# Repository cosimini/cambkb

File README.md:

# Yet another split keyboard with low profile Gateron switches

**Important note: tested, it works**
Now the hard part, try getting used to it.

**WARNING:** There's a mistake in the RJ-9 connector routing, I didn't consider that RJ9 cables are typically crimped mirrored, so a custom cable has to be made in order to use the design.

Basically a replica of any other split keyboard project you can find on github
* Pro micro controller
* Gateron low profile KS-33 switches with hot-swap sockets
* No OLED screen, LEDs or other shiny stuff

The main difference in the layout is that the positions of the thumb-keys is moved to the center with respect to more famous keyboards like the Lily58, more like the Voyager.
Vertical stagging of about 1/4 of a key size is applied in the vertical direction, between columns.
The distance between switches is 19mm and not 19.05mm like many other, I don't care it's not 3/4 of an inch.

The PCB is designed using KiCad. It is the same for both right and left side, depending on where components are soldered.
There's no 3D printed case or key support mask, but I'd like to implement it.

The reason for the double socket for the controller is that I was usure on which side I'd like to put the controller.

For the time being I'm not planning to implement QMK or similar things, key map is hardcoded in the code.
The code is based on the Arduino library because I'm lazy. For the same reason I'm using PlatformIO.

For the used switches and controller lib/footprint, credit to [foostan/kdb](https://github.com/foostan/kbd/tree/main).

# BOM
* Controllers: Any pro-micro close is fine, I used the cheapest one I found on Amazon. You can buy presoldered ones, the PCB is compatible with any orientation.
* Switches: Gatheron low profile switches, KS-33 footprint, I used [those ones](https://www.gateron.com/products/gateron-ks-33-low-profile-20-banana-switch?VariantsId=10734).
* Sockets for the switches: The ones associated to the KS-33 footprint ([those](https://www.gateron.com/products/gateron-low-profile-switch-hot-swap-pcb-socket?VariantsId=10234)).
* Diodes: BAT85 are the ones I used, but any signal diode with similar specs should be fine.
* Resistors: There's a resistor in series to the voltage sourcing pin. To prevent accidental shorts, a 1k resistor is placed in series. Those can be replaced by a jumper wire. Note I used DIN0204, a kind of small size trough hole package.
* Sockets for the controller: If you don't want to solder the controllers to the PCB, you can use any 2.54mm socket.
* RJ9 socket: It is a standard, any trough hole socket is fine.
* RJ9 Cable: **WARNING** as mentioned above, you need to make your own cable, as the common telephone ones has mirrored connected plugs at each end (i.e. in my design each cable must end on the same size of the plug).

# Pictures of the result

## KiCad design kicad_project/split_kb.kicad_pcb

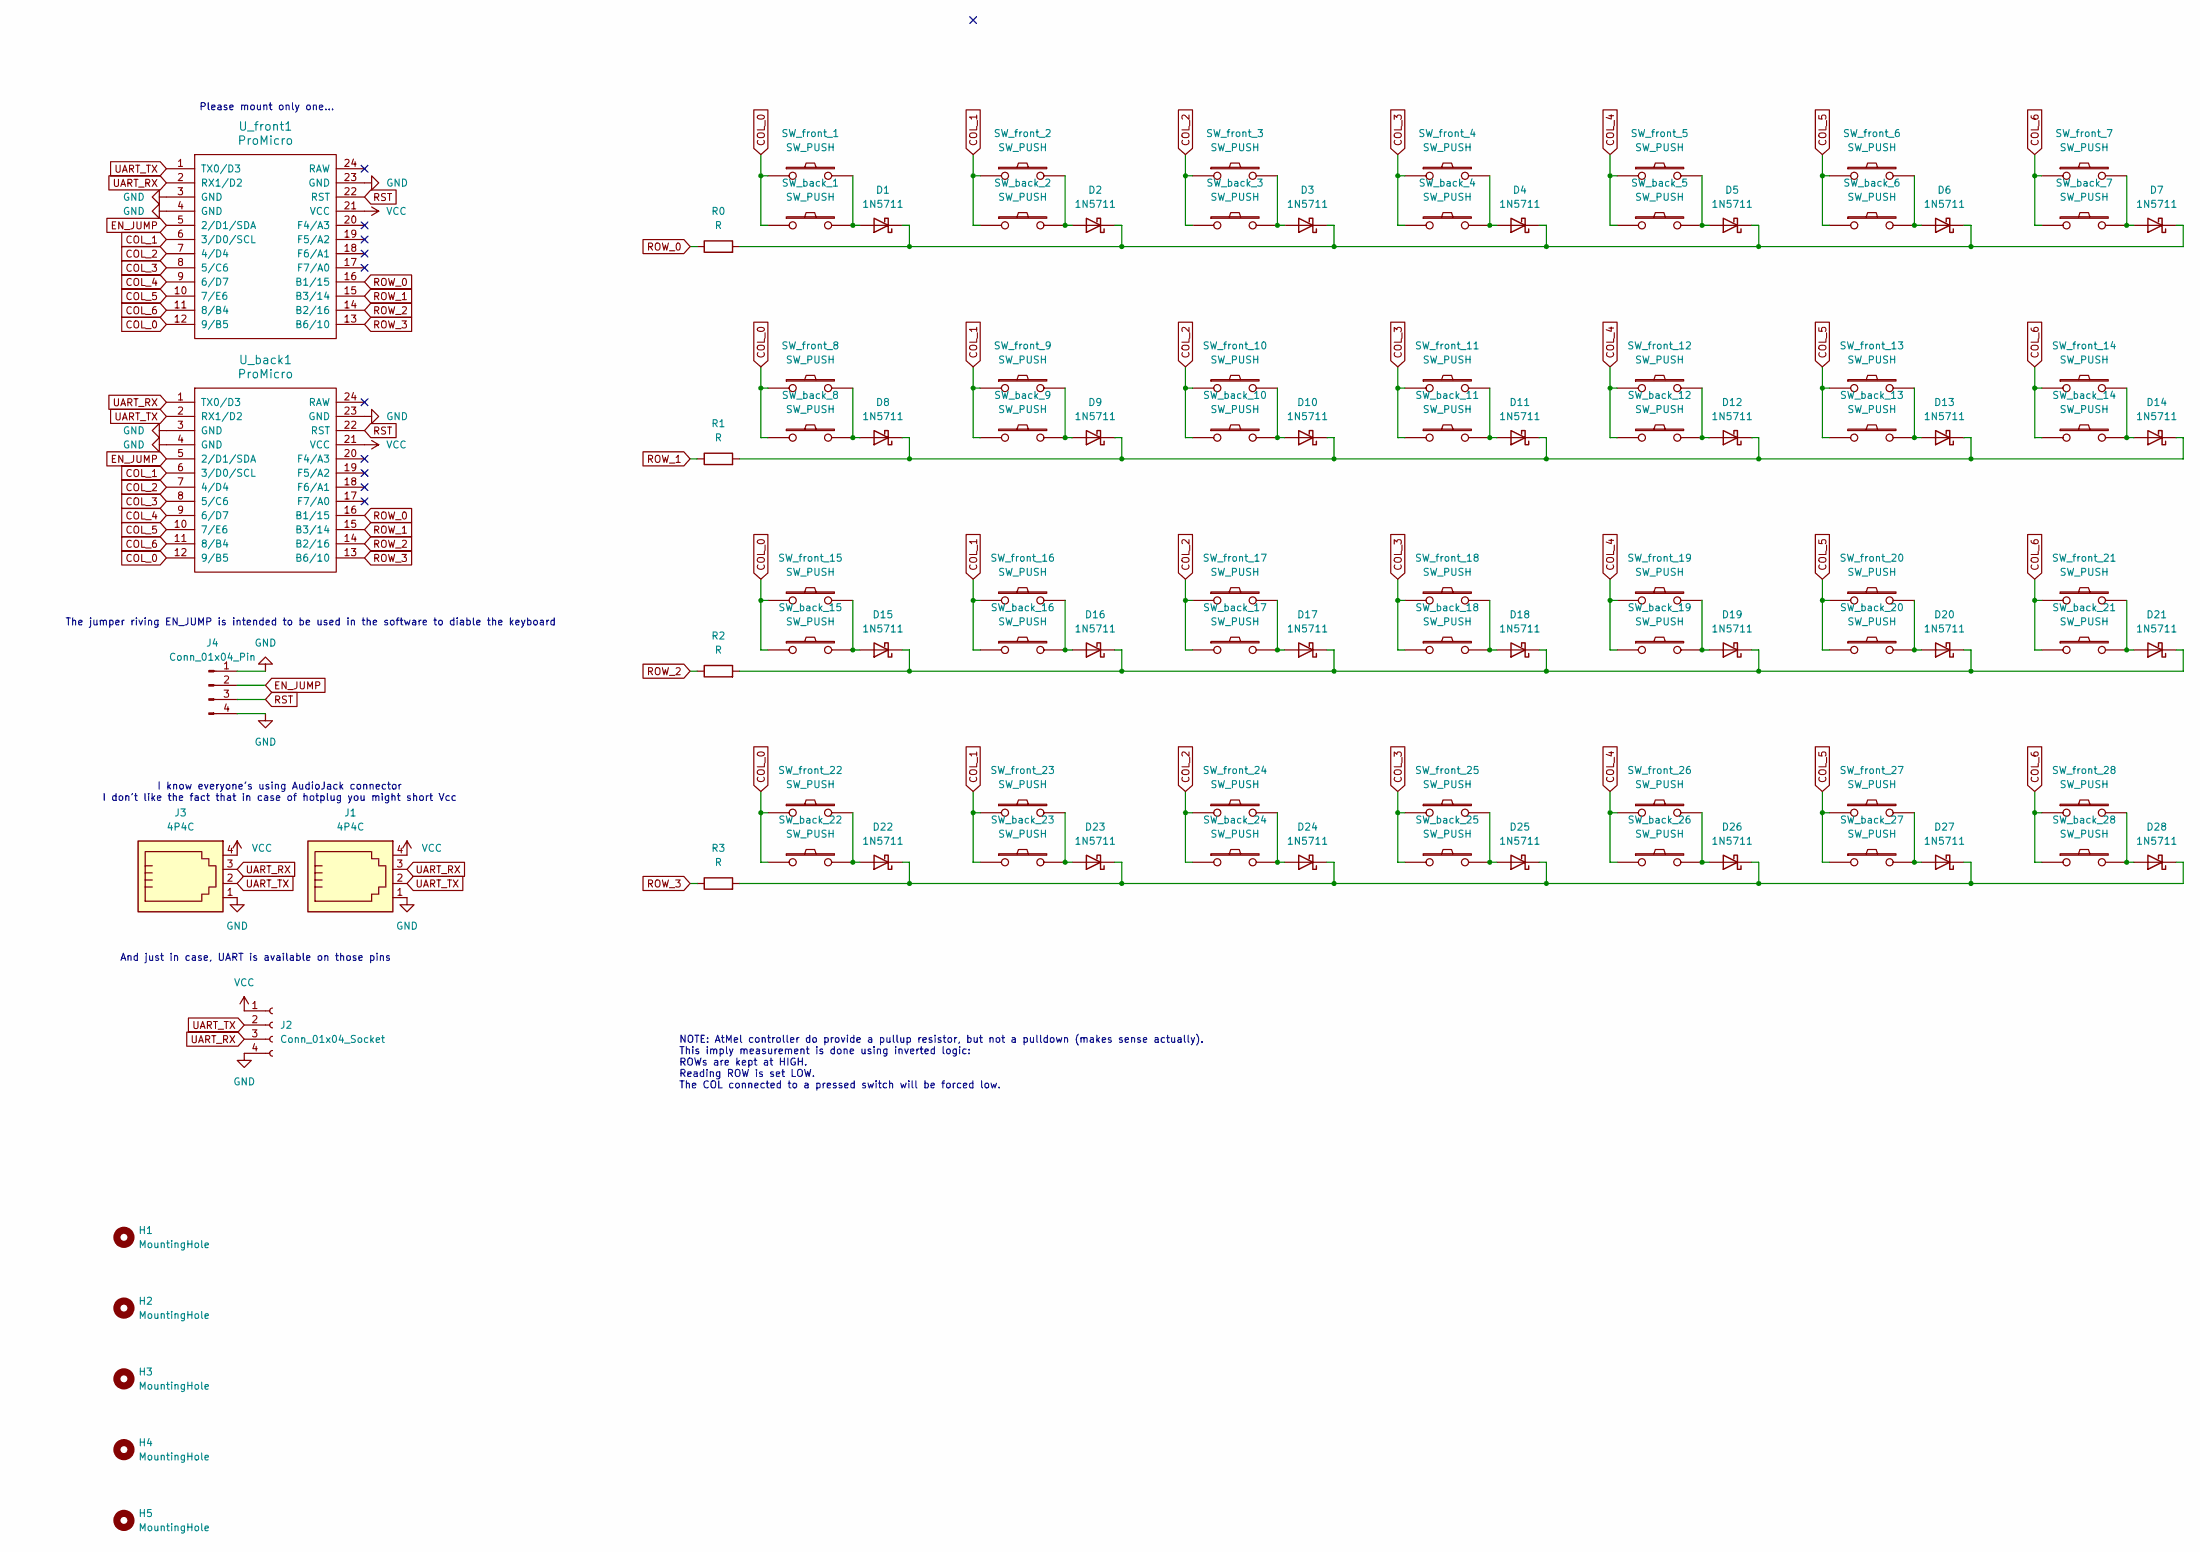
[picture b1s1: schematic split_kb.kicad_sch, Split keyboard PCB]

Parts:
D1, D2, D3, D4, D5, D6, D7, D8, D9, D10, D11, D12, D13, D14, D15, D16, D17, D18, D19, D20, D21, D22, D23, D24, D25, D26, D27, D28: 1N5711; D_DO-35_SOD27_P7.62mm_Horizontal
H1, H2, H3, H4, H5: MountingHole; MountingHole_3mm_Pad_Via
J1, J3: 4P4C; RJ9_Evercom_5301-440xxx_Horizontal
J2: Conn_01x04_Socket; PinHeader_1x04_P2.54mm_Vertical
J4: Conn_01x04_Pin; PinHeader_1x04_P2.54mm_Vertical
R0, R1, R2, R3: R; R_Axial_DIN0204_L3.6mm_D1.6mm_P5.08mm_Horizontal
SW_back_1, SW_back_2, SW_back_3, SW_back_4, SW_back_5, SW_back_6, SW_back_7, SW_back_8, SW_back_9, SW_back_10, SW_back_11, SW_back_12, SW_back_13, SW_back_14, SW_back_15, SW_back_16, SW_back_17, SW_back_18, SW_back_19, SW_back_20, SW_back_21, SW_back_22, SW_back_23, SW_back_24, SW_back_25, SW_back_26, SW_back_27, SW_back_28: SW_PUSH; keyswitch_gateron_low_profile_hotswap_1u
SW_front_1, SW_front_2, SW_front_3, SW_front_4, SW_front_5, SW_front_6, SW_front_7, SW_front_8, SW_front_9, SW_front_10, SW_front_11, SW_front_12, SW_front_13, SW_front_14, SW_front_15, SW_front_16, SW_front_17, SW_front_18, SW_front_19, SW_front_20, SW_front_21, SW_front_22, SW_front_23, SW_front_24, SW_front_25, SW_front_26, SW_front_27, SW_front_28: SW_PUSH; keyswitch_gateron_low_profile_hotswap_1u
U_back1: ProMicro
U_front1: ProMicro

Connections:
COL_0: SW_back_1.1, SW_back_8.1, SW_back_15.1, SW_back_22.1, SW_front_1.1, SW_front_8.1, SW_front_15.1, SW_front_22.1, U_back1.12 (9/B5), U_front1.12 (9/B5)
COL_1: SW_back_2.1, SW_back_9.1, SW_back_16.1, SW_back_23.1, SW_front_2.1, SW_front_9.1, SW_front_16.1, SW_front_23.1, U_back1.6 (3/D0/SCL), U_front1.6 (3/D0/SCL)
COL_2: SW_back_3.1, SW_back_10.1, SW_back_17.1, SW_back_24.1, SW_front_3.1, SW_front_10.1, SW_front_17.1, SW_front_24.1, U_back1.7 (4/D4), U_front1.7 (4/D4)
COL_3: SW_back_4.1, SW_back_11.1, SW_back_18.1, SW_back_25.1, SW_front_4.1, SW_front_11.1, SW_front_18.1, SW_front_25.1, U_back1.8 (5/C6), U_front1.8 (5/C6)
COL_4: SW_back_5.1, SW_back_12.1, SW_back_19.1, SW_back_26.1, SW_front_5.1, SW_front_12.1, SW_front_19.1, SW_front_26.1, U_back1.9 (6/D7), U_front1.9 (6/D7)
COL_5: SW_back_6.1, SW_back_13.1, SW_back_20.1, SW_back_27.1, SW_front_6.1, SW_front_13.1, SW_front_20.1, SW_front_27.1, U_back1.10 (7/E6), U_front1.10 (7/E6)
COL_6: SW_back_7.1, SW_back_14.1, SW_back_21.1, SW_back_28.1, SW_front_7.1, SW_front_14.1, SW_front_21.1, SW_front_28.1, U_back1.11 (8/B4), U_front1.11 (8/B4)
EN_JUMP: J4.2, U_back1.5 (2/D1/SDA), U_front1.5 (2/D1/SDA)
GND: J1.1, J2.4, J3.1, J4.1, J4.4, U_back1.3 (GND), U_back1.4 (GND), U_back1.23 (GND), U_front1.3 (GND), U_front1.4 (GND), U_front1.23 (GND)
unnamed: D1.2 (A), SW_back_1.2, SW_front_1.2
unnamed: D1.1 (K), D2.1 (K), D3.1 (K), D4.1 (K), D5.1 (K), D6.1 (K), D7.1 (K), R0.2
unnamed: D2.2 (A), SW_back_2.2, SW_front_2.2
unnamed: D3.2 (A), SW_back_3.2, SW_front_3.2
unnamed: D4.2 (A), SW_back_4.2, SW_front_4.2
unnamed: D5.2 (A), SW_back_5.2, SW_front_5.2
unnamed: D6.2 (A), SW_back_6.2, SW_front_6.2
unnamed: D7.2 (A), SW_back_7.2, SW_front_7.2
unnamed: D8.2 (A), SW_back_8.2, SW_front_8.2
unnamed: D9.2 (A), SW_back_9.2, SW_front_9.2
unnamed: D10.2 (A), SW_back_10.2, SW_front_10.2
unnamed: D8.1 (K), D9.1 (K), D10.1 (K), D11.1 (K), D12.1 (K), D13.1 (K), D14.1 (K), R1.2
unnamed: D11.2 (A), SW_back_11.2, SW_front_11.2
unnamed: D12.2 (A), SW_back_12.2, SW_front_12.2
unnamed: D13.2 (A), SW_back_13.2, SW_front_13.2
unnamed: D14.2 (A), SW_back_14.2, SW_front_14.2
unnamed: D15.2 (A), SW_back_15.2, SW_front_15.2
unnamed: D15.1 (K), D16.1 (K), D17.1 (K), D18.1 (K), D19.1 (K), D20.1 (K), D21.1 (K), R2.2
unnamed: D16.2 (A), SW_back_16.2, SW_front_16.2
unnamed: D17.2 (A), SW_back_17.2, SW_front_17.2
unnamed: D18.2 (A), SW_back_18.2, SW_front_18.2
unnamed: D19.2 (A), SW_back_19.2, SW_front_19.2
unnamed: D20.2 (A), SW_back_20.2, SW_front_20.2
unnamed: D21.2 (A), SW_back_21.2, SW_front_21.2
unnamed: D22.2 (A), SW_back_22.2, SW_front_22.2
unnamed: D22.1 (K), D23.1 (K), D24.1 (K), D25.1 (K), D26.1 (K), D27.1 (K), D28.1 (K), R3.2
unnamed: D23.2 (A), SW_back_23.2, SW_front_23.2
unnamed: D24.2 (A), SW_back_24.2, SW_front_24.2
unnamed: D25.2 (A), SW_back_25.2, SW_front_25.2
unnamed: D26.2 (A), SW_back_26.2, SW_front_26.2
unnamed: D27.2 (A), SW_back_27.2, SW_front_27.2
unnamed: D28.2 (A), SW_back_28.2, SW_front_28.2
ROW_0: R0.1, U_back1.16 (B1/15), U_front1.16 (B1/15)
ROW_1: R1.1, U_back1.15 (B3/14), U_front1.15 (B3/14)
ROW_2: R2.1, U_back1.14 (B2/16), U_front1.14 (B2/16)
ROW_3: R3.1, U_back1.13 (B6/10), U_front1.13 (B6/10)
RST: J4.3, U_back1.22 (RST), U_front1.22 (RST)
UART_RX: J1.3, J2.3, J3.3, U_back1.1 (TX0/D3), U_front1.2 (RX1/D2)
UART_TX: J1.2, J2.2, J3.2, U_back1.2 (RX1/D2), U_front1.1 (TX0/D3)
VCC: J1.4, J2.1, J3.4, U_back1.21 (VCC), U_front1.21 (VCC)

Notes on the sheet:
And just in case, UART is available on those pins
Please mount only one...
I know everyone's using AudioJack connector I don't like the fact that in case of hotplug you might short Vcc
NOTE: AtMel controller do provide a pullup resistor, but not a pulldown (makes sense actually). This imply measurement is done using inverted logic: ROWs are kept at HIGH. Reading ROW is set LOW. The COL connected to a pressed switch will be forced low.
The jumper riving EN_JUMP is intended to be used in the software to diable the keyboard

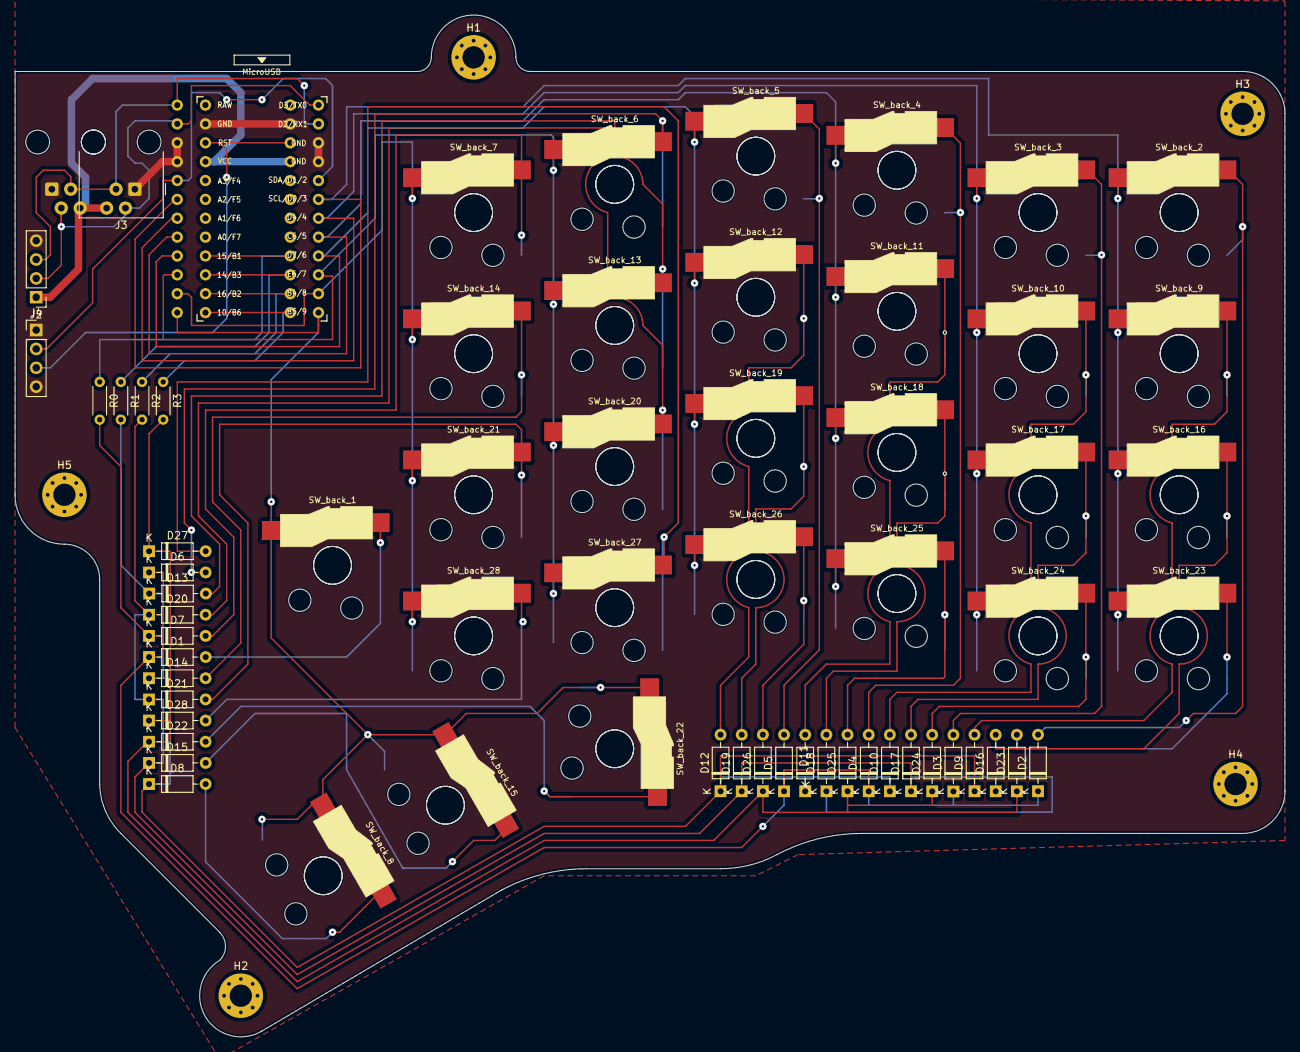
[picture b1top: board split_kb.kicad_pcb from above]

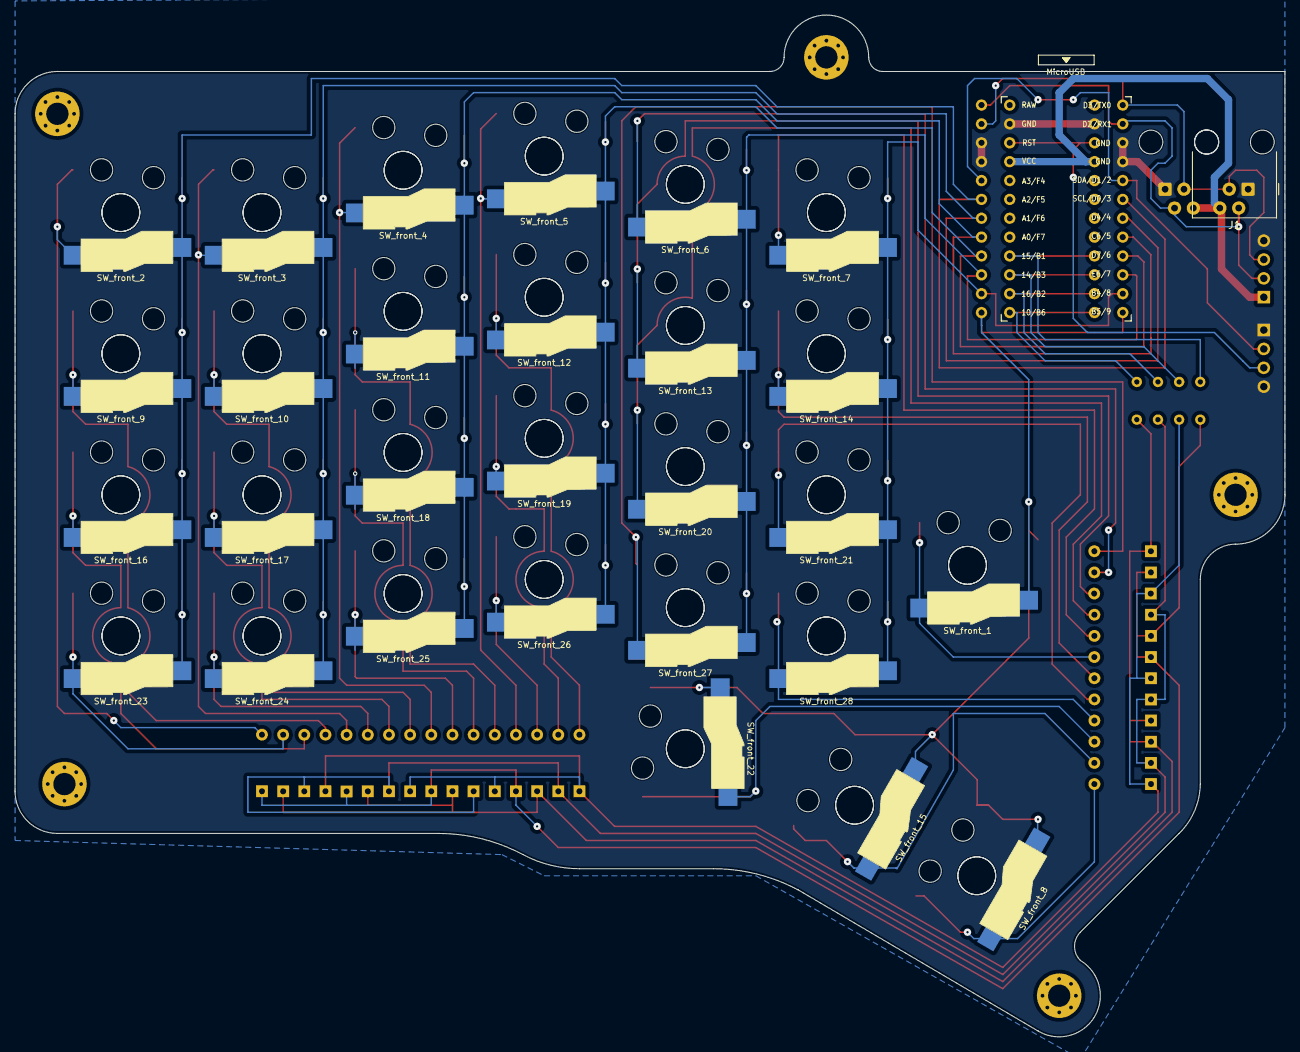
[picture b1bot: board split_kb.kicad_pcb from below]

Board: 2 copper layers, 171.0 x 137.6 mm, 99 parts (30 on the bottom side), 49 nets.

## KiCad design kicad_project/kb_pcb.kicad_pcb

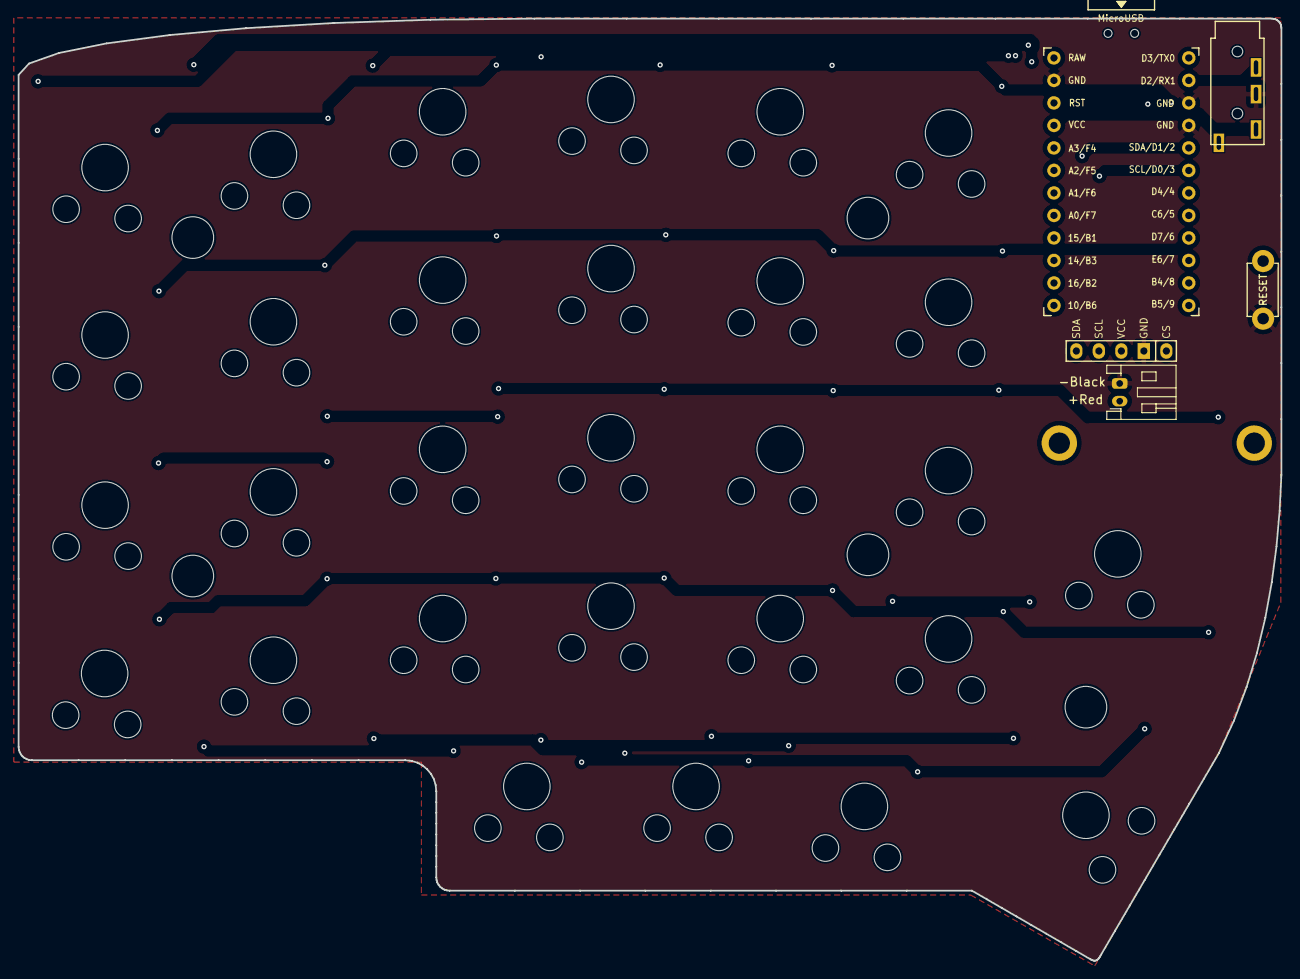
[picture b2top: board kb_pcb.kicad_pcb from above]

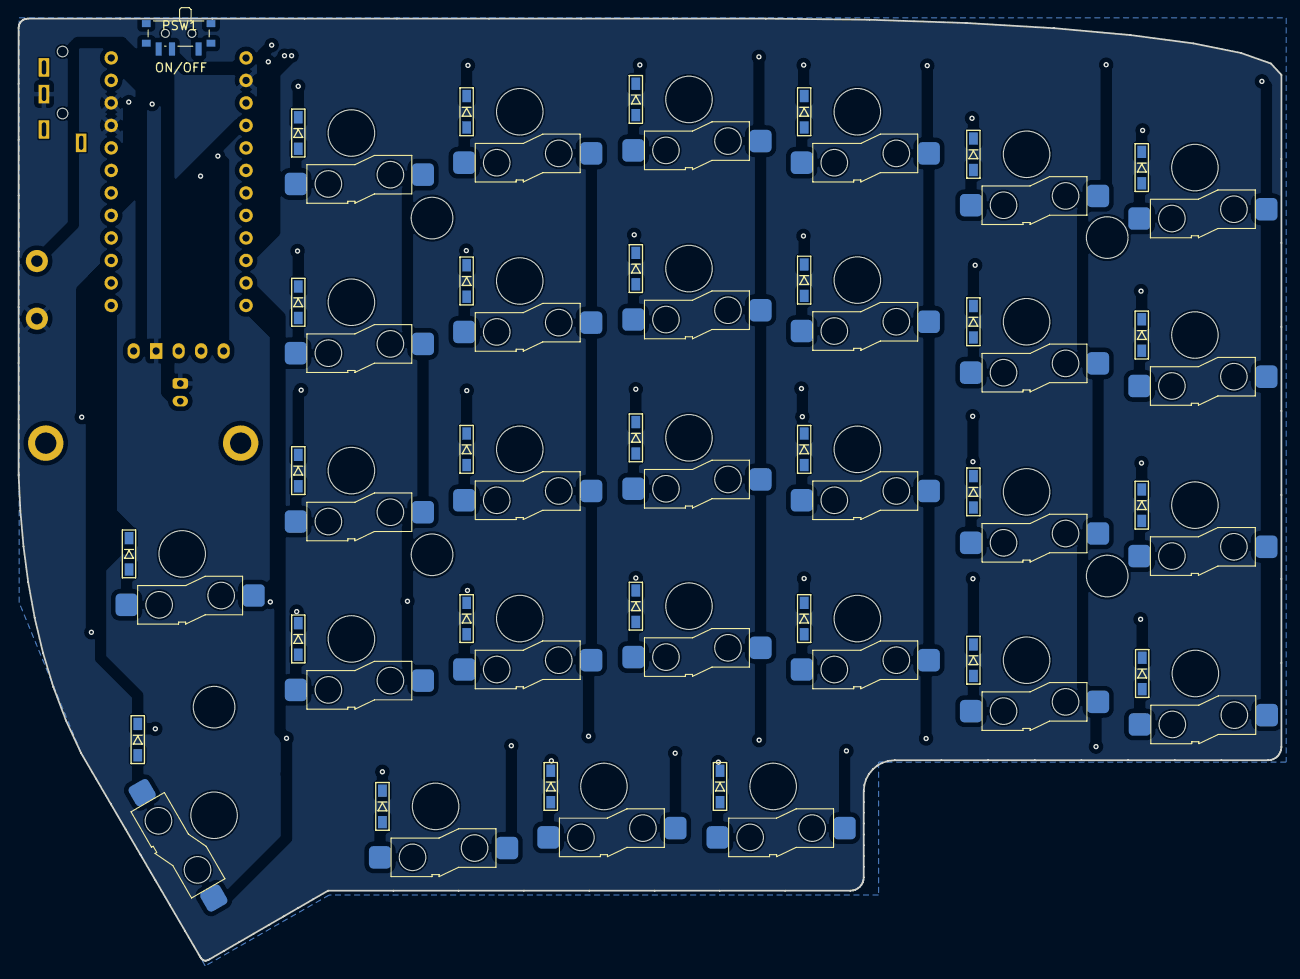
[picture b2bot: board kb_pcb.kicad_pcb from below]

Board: 2 copper layers, 142.5 x 106.3 mm, 71 parts (37 on the bottom side), 49 nets, no tracks yet.

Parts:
BATJ1: Conn_01x02_Female; JST_PH_S2B-PH-K_1x02_P2.00mm_Horizontal
D1, D2, D3, D4, D5, D6, D7, D8, D9, D10, D11, D12, D13, D14, D15, D16, D17, D18, D19, D20, D21, D22, D23, D24, D25, D26, D27, D28, D29: D; D3_SMD_v2
J2: 4PIN; MJ-4PP-9
J3: OLED; nice_view_1side
PSW1: SW_SPST; SW_SPDT_PCM12
RSW1: SW_RST; TACT_SWITCH_TVBP06
SW1, SW2, SW3, SW4, SW5, SW6, SW7, SW8, SW9, SW10, SW11, SW12, SW13, SW14, SW15, SW16, SW17, SW18, SW19, SW20, SW21, SW22, SW23, SW24, SW25, SW26, SW27, SW28, SW29: SW_PUSH; SW_Gateron_LowProfile_HotSwap
TH1, TH2: HOLE; M2_HOLE_PCB
TH3, TH4, TH5, TH6, TH7: HOLE; HOLE_M2_TH
U1: ProMicro; ProMicro_v3

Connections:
+BATT: BATJ1.1, PSW1.3 (C)
CS: J3.5, U1.1 (TX(PD3))
DATA: J2.3, U1.2 (RX(PD2))
GND: BATJ1.2, J2.2, J3.4, RSW1.1, U1.3 (GND), U1.4 (GND), U1.23 (GND)
unnamed: D1.2 (A), SW1.2
unnamed: D2.2 (A), SW2.2
unnamed: D3.2 (A), SW3.2
unnamed: D4.2 (A), SW4.2
unnamed: D5.2 (A), SW5.2
unnamed: D6.2 (A), SW6.2
unnamed: D7.2 (A), SW7.2
unnamed: D8.2 (A), SW8.2
unnamed: D9.2 (A), SW9.2
unnamed: D10.2 (A), SW10.2
unnamed: D11.2 (A), SW11.2
unnamed: D12.2 (A), SW12.2
unnamed: D13.2 (A), SW13.2
unnamed: D14.2 (A), SW14.2
unnamed: D15.2 (A), SW15.2
unnamed: D16.2 (A), SW16.2
unnamed: D17.2 (A), SW17.2
unnamed: D18.2 (A), SW18.2
unnamed: D19.2 (A), SW19.2
unnamed: D20.2 (A), SW20.2
unnamed: D21.2 (A), SW21.2
unnamed: D22.2 (A), SW22.2
unnamed: D23.2 (A), SW23.2
unnamed: D24.2 (A), SW24.2
unnamed: D25.2 (A), SW25.2
unnamed: D26.2 (A), SW26.2
unnamed: D27.2 (A), SW27.2
unnamed: D28.2 (A), SW28.2
unnamed: D29.2 (A), SW29.2
RESET: RSW1.2, U1.22 (RST)
SCL: J3.2, U1.6 (SCL(PD0))
SDA: J3.1, U1.5 (SDA(PD1))
VCC: J2.1, J3.3, U1.21 (VCC)
col0: SW6.1, SW12.1, SW18.1, SW24.1, U1.18 (A1(PF6))
col1: SW5.1, SW11.1, SW17.1, SW23.1, SW29.1, U1.17 (A0(PF7))
col2: SW4.1, SW10.1, SW16.1, SW22.1, SW28.1, U1.16 (D15(PB1))
col3: SW3.1, SW9.1, SW15.1, SW21.1, SW27.1, U1.15 (D14(PB3))
col4: SW2.1, SW8.1, SW14.1, SW20.1, SW26.1, U1.14 (D16(PB2))
col5: SW1.1, SW7.1, SW13.1, SW19.1, SW25.1, U1.13 (D10(PB6))
raw: PSW1.2 (B), U1.24 (RAW)
row0: D1.1 (K), D2.1 (K), D3.1 (K), D4.1 (K), D5.1 (K), D6.1 (K), U1.8 (D5(PC6))
row1: D7.1 (K), D8.1 (K), D9.1 (K), D10.1 (K), D11.1 (K), D12.1 (K), U1.9 (D6(PD7))
row2: D13.1 (K), D14.1 (K), D15.1 (K), D16.1 (K), D17.1 (K), D18.1 (K), U1.10 (D7(PE6))
row3: D19.1 (K), D20.1 (K), D21.1 (K), D22.1 (K), D23.1 (K), D24.1 (K), U1.11 (D8(PB4))
row4: D25.1 (K), D26.1 (K), D27.1 (K), D28.1 (K), D29.1 (K), U1.12 (D9(PB5))

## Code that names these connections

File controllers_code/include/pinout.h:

/*
* Define pinout
*/

#define ROW0 15
#define ROW1 14
#define ROW2 16
#define ROW3 10

#define COL0 9
#define COL1 3
#define COL2 4
#define COL3 5
#define COL4 6
#define COL5 7
#define COL6 8

#define EN_PIN 2

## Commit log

2024-04-14 Credits for the library
2024-04-14 Add kicad project.
2024-04-14 Add .gitignore
2024-04-19 Done the hard operation of traking between holes
2024-04-19 Add gitignore (again)
2024-04-21 Completed first draft of the PCB
2024-04-21 I will have to remove the rounded corners from the layout, too many errors
2024-04-22 Fixed edge cut error, changed vertical stagging a bit
2024-04-22 Moved one of the holes up
2024-04-22 Grounded EN pin, moved a mounting hole
2024-04-23 Minor changes
2024-04-23 Remove pushbutton library (I removed the reset switch)
2024-04-27 Move trace far from mounting hole, add screenshot
2024-04-28 Generated production files for JLCPCB
2024-05-02 Add keymaps.h, idiot 4 keys library test on main.c
2024-05-03 Move test code to a new project
2024-05-07 Some work on the code (it's becaming a mess already)
2024-05-09 PCB arrived! Writing some test code
2024-05-09 Merda, non riesco ad attivare i pull-up nel controllore
2024-05-11 Actually, with another test code, the pullups are working
2024-05-11 FOUND THE BUG: I was configuring the pins up to n_row, not up to n_cols
2024-05-11 Fix pinout
2024-05-11 Debug code in controller code to check hardware
2024-05-11 Better debug code
2024-05-12 Start implementing the key map logic
2024-05-25 Replace variable with define
2024-05-30 Some work on the code (and the cable socket has wrong connections)
2024-06-01 First, failed, tentative of making the code work
2024-06-02 Half of the kb is working, unable to send keystrokes over UART ATM
2024-06-03 Test the UART communication
2024-06-05 Commit before changing the code structure
2024-06-06 Writing this commit with the new keyboard!
2024-06-07 Clean up the code, update map
2024-06-11 Fix slave layers, update keymap
2024-06-16 Fix backslash key not working
2024-06-16 Add photos
2024-06-16 Add cable error warning
2024-06-16 Replace come const with compiler definitions
2024-06-17 Remove old test code
2024-06-17 Remove unused files
2024-06-18 Move to simple 2 layers layout
2024-08-11 Update keymap
2024-08-14 Add BOM description
    Did not include links for stuff that can be found from different distributors
2025-03-12 Last keymap
2025-03-12 Add a sketch of the new code implemeting low key count and tap-hold stuff
2025-03-12 Remove prefectly useless folders considering the complexity of the project
